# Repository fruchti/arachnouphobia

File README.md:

# Arachnouphobia

This is a small WS2812B strip controller based on a STM32F030F4P6 whose only job it is to deliver random light flashes. This is surprisingly effective to deter spiders! More information can be found [here](https://25120.org/post/arachnouphobia/).

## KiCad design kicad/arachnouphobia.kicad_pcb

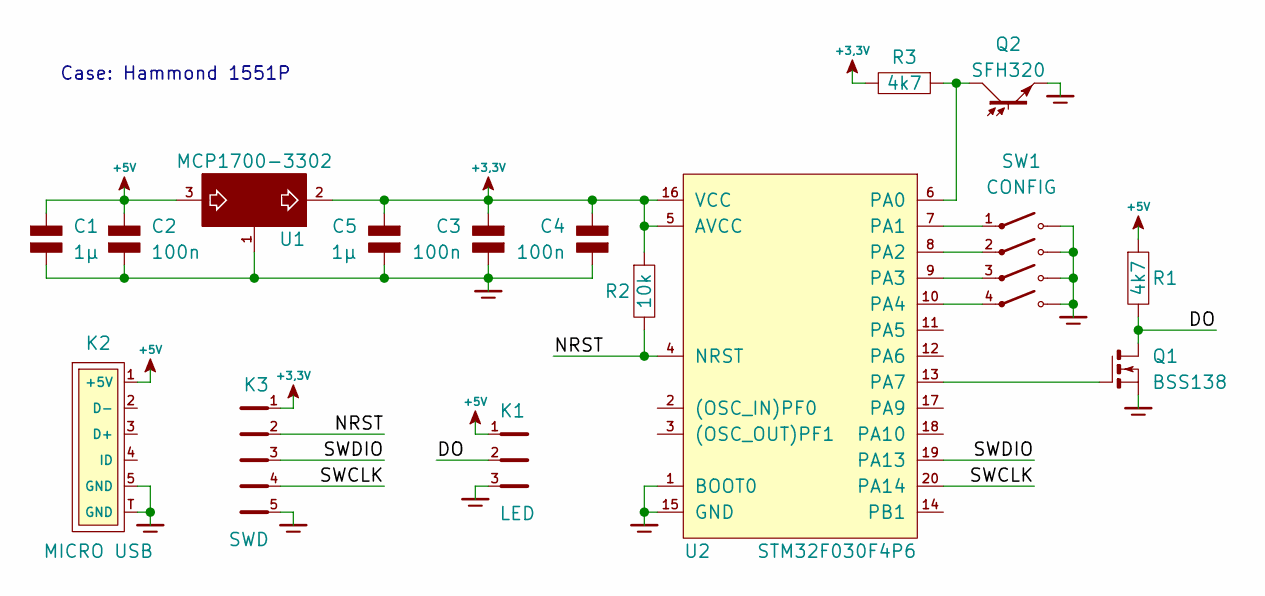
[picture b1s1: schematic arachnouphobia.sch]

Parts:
C1, C5: 1µ; 0603_B
C2, C3, C4: 100n; 0603_B
K1: LED; PSS254-3W
K2: MICRO USB; USB_B_MICRO_W_SMT_AMPHENOL_10103593
K3: SWD; PINHEAD_1_5
Q1: BSS138; SOT23
Q2: SFH320; LED_5mm_100
R1, R3: 4k7; 0603_B
R2: 10k; 0603_B
SW1: CONFIG; DIP8_300
U1: MCP1700-3302; SOT23
U2: STM32F030F4P6; TSSOP20

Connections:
+3,3V: C3.1, C4.1, C5.1, K3.1, R2.1, R3.2, U1.2 (VO), U2.5 (AVCC), U2.16 (VCC)
+5V: C1.1, C2.1, K1.1, K2.1 (+5V), R1.1, U1.3 (VI)
/DO: K1.2, Q1.3 (D), R1.2
/NRST: K3.2, R2.2, U2.4 (NRST)
/SWCLK: K3.4, U2.20 (PA14)
/SWDIO: K3.3, U2.19 (PA13)
GND: C1.2, C2.2, C3.2, C4.2, C5.2, K1.3, K2.5 (GND), K2.T (GND), K3.5, Q1.2 (S), Q2.1 (E), SW1.5, SW1.6, SW1.7, SW1.8, U1.1 (GND), U2.1 (BOOT0), U2.15 (GND)
unnamed: Q1.1 (G), U2.13 (PA7)
unnamed: Q2.2 (C), R3.1, U2.6 (PA0)
unnamed: SW1.1, U2.7 (PA1)
unnamed: SW1.2, U2.8 (PA2)
unnamed: SW1.3, U2.9 (PA3)
unnamed: SW1.4, U2.10 (PA4)

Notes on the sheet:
Case: Hammond 1551P

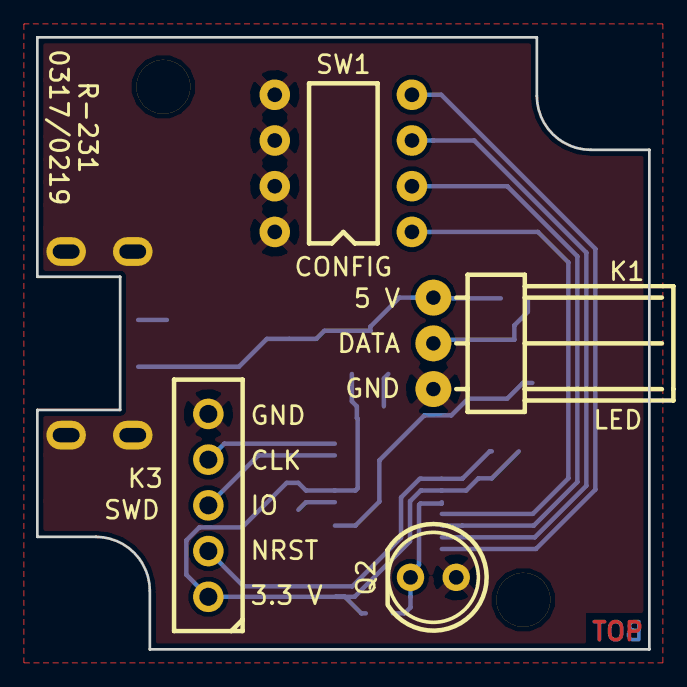
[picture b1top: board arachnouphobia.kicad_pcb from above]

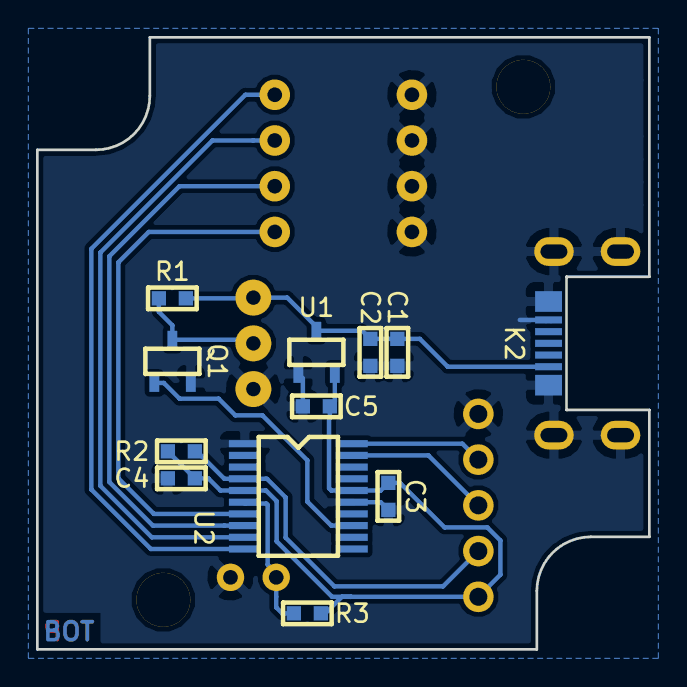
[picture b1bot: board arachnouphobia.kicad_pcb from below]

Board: 2 copper layers, 34.0 x 34.0 mm, 18 parts (12 on the bottom side), 13 nets.

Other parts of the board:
HOLE_3mm, HOLE_3mm#2: VAL**; HOLE_3mm

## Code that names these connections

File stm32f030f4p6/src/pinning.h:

#ifndef PINNING_H_
#define PINNING_H_

#define PIN_SENSOR      0   // PA0 - light sensor
#define PIN_DIP_1       4   // PA1 - DIP switch 1
#define PIN_DIP_2       3   // PA2 - DIP switch 2
#define PIN_DIP_3       2   // PA3 - DIP switch 3
#define PIN_DIP_4       1   // PA4 - DIP switch 4

#endif

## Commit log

2019-11-08 Add KiCad schematic and layout
2019-11-08 Add STM32F0 firmware
2019-11-08 Add copper layer PDF and gerber files
2019-11-08 Add ATTiny24 single-LED experiment firmware
2019-11-12 Add README
